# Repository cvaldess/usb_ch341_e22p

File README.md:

# usb_ch341_e22p

**USB → SPI** adapter for using an **EBYTE E22P-868M30S** LoRa module (SX1262 + PA, 30 dBm / 1 W) with **[meshtasticd](https://meshtastic.org/docs/software/linux/)** on a PC or a Raspberry Pi, with no GPIO needed.

The bridge is a **CH341F** in UIO mode, the mode supported by Meshtastic's [`libch341-spi-userspace`](https://github.com/meshtastic/libch341-spi-userspace) driver. A **TPS2115A** power multiplexer switches automatically between USB power and a DC jack, so the module can transmit at full power without overloading the computer's port.

---

## Specifications

| | |
|---|---|
| PCB | 49.22 × 63.54 mm · **2 layers** · 1.6 mm · vias 0.6/0.3 mm |
| USB bridge | CH341F (QFN-28), parallel/synchronous mode (PID `0x5512`) |
| Radio | EBYTE E22P-868M30S — SX1262 + PA, up to **30 dBm**, 868 MHz |
| Power | USB-C 5 V **or** 5 V DC jack (2.5 mm), automatic switchover |
| Current limit | 1.28 A nominal (TPS2115A with `R8` = 390 Ω) |
| Logic | 3.3 V (XC6206 LDO), the E22P's logic level |
| Antenna | Right-angle female SMA, 50 Ω |
| Configuration | 24C02 EEPROM for VID/PID/mode |

## How the power path works

This is the least obvious part of the design. The E22P draws **600–670 mA when transmitting at 30 dBm**, more than a USB port guarantees (500 mA). The board handles this with a multiplexer whose source selection is **deterministic**, not based on comparing voltages:

| USB | Jack | `D1` | `D0` | Active source | LED `D4` |
|:---:|:----:|:----:|:----:|---|:---:|
| ✅ | ❌ | 0 | 0 | **USB** — use reduced power | off |
| ✅ | ✅ | 1 | 0 | **Jack** — full power | **on** |
| ❌ | ✅ | 0 | 0 | none (Hi-Z) | — |
| ❌ | ❌ | 0 | 0 | none (Hi-Z) | — |

`D0` is tied to ground and `D1` is driven by the jack's switch contact, with `R7` (10 kΩ) pulled up to **VBUS**. So `D1` encodes *"jack present **and** USB present"*, which gives two useful properties:

- With the jack plugged in, **the jack always wins**, whichever source has the higher voltage (both useful rows use `D0`=0, where the TPS2115A truth table ignores the `IN2>IN1` comparison).
- **Without USB the module is left unpowered**, which is intended: the board is useless when disconnected from the host, and this prevents a powered E22P from back-feeding current through the pins of an unpowered CH341.

LED `D4` hangs off `STAT`, which is open-drain and pulls low when `IN1` is active: **on = running from the jack**.

## meshtasticd configuration

The CH341 pins are numbered as UIO lines `D0`–`D7`. This board's pin mapping matches the official `lora-usb-meshtoad-e22.yaml` preset:

```yaml
Lora:
  Module: sx1262
  CS: 0        # D0 · pin 15 → NSS
  RXen: 1      # D1 · pin 16 → EN   (RF front-end enable)
  Reset: 2     # D2 · pin 17 → NRST
  Busy: 4      # D4 · pin 19 → BUSY
  IRQ: 6       # D6 · pin 21 → DIO1
  spidev: ch341
  DIO2_AS_RF_SWITCH: true
  DIO3_TCXO_VOLTAGE: true
  USB_VID: 0x1A86
  USB_PID: 0x5512
  # When powered ONLY from USB, lower the power so the port is not overloaded:
  # SX126X_MAX_POWER: 10
```

`SCK` is on `D3` (pin 18) and `MOSI` on `D5` (pin 20); `MISO` is on `D7` (pin 22), which, like `D6`, is a fixed input on the CH341. `DIO2_AS_RF_SWITCH` is mandatory: on the board, the `DIO2` pin is bridged to `T/R CTRL`, as note ① of the EBYTE manual specifies.

> [!IMPORTANT]
> **EEPROM `U2` must be programmed** with `MODE = 0x12` for the CH341 to enumerate as a parallel/synchronous port. Unprogrammed, the chip reads floating `SDA`/`SCL` and boots as a **serial port**, not as SPI. It is programmed over USB with `CH341CFG` or `IMSProg`.

## Manufacturing

Everything you need is in [`fab/`](fab/):

| File | Purpose |
|---|---|
| `gerbers-pcbway.zip` | Gerbers + drill files + drill maps, ready to upload to PCBWay |
| `bom-pcbway.csv` | Bill of materials: manufacturer, part number, LCSC code and assembly notes |
| `centroid-pcbway.csv` | Placement positions for assembly (the 34 SMD parts) |
| `*-drl_map.pdf` | Drill map, for a quick visual check |
| `*.gtp` / `*.gbp` | Paste layers, in case you order a stencil |

Parameters: **2 layers, 1.6 mm, HASL or ENIG**. Nothing beyond standard capabilities. The stencil is **single-sided** (top): the bottom paste layer is empty.

### BOM notes

- **Every part has an LCSC code**, passives included. The code for `U3` (E22P-868M30S, `C51912689`) is only in the BOM, not in the schematic.
- **`SMA1` is through-hole**: it is in the BOM but not in the centroid file, and is soldered after reflow. The 4 shell legs of `USB1` are through-hole too.
- **The centroid gives the centre of each part's body.** For `U3`, `USB1` and `U6` this is not the footprint origin (it is 1.41, 1.15 and 0.65 mm away); the BOM says so in their notes.

## Main components

| Ref | Part | Function |
|---|---|---|
| `U1` | CH341F | USB ↔ SPI bridge |
| `U2` | 24C02 | Configuration EEPROM (VID/PID/mode) |
| `U3` | E22P-868M30S | SX1262 + PA LoRa module |
| `U4` | XC6206P332MR | 3.3 V LDO for the CH341 |
| `U5` | TPS2115A | Power multiplexer |
| `U6` | DC-005-2.5A | 5 V DC jack with switch contact |
| `U7` | H7VHD3UA | TVS protection on VBUS |
| `D2` | TPD4E05U06 | USB ESD protection (D+/D−/CC1/CC2) |
| `C5` | 470 µF / 16 V | Solid polymer, 28 mΩ ESR — reservoir for TX peaks |

## Datasheets

The PDFs are not included in the repository (they are copyrighted by their manufacturers). Links to the sources:

- [CH341 (WCH)](https://www.wch-ic.com/products/CH341.html) · [E22P-868M30S (EBYTE)](https://www.cdebyte.com/products/E22P-868M30S) · [TPS2115A (TI)](https://www.ti.com/product/TPS2115A) · [TPD4E05U06 (TI)](https://www.ti.com/product/TPD4E05U06) · [XC6206 (Torex)](https://www.torexsemi.com/products/voltage-regulators/xc6206/)
- LCSC references: `C412870` (CH341F) · `C2863458` (TPS2115A) · `C138714` (TPD4E05U06) · `C20615807` (H7VHD3UA) · `C709357` (USB-C) · `C2880544` (jack) · `C9002` (crystal)

## Known limitations

- **No protection on the jack input.** There is no TVS and no reverse-polarity protection on `IN1`. The E22P is damaged above 5.5 V and the TPS2115A has an absolute maximum of 6 V: a 9 V or 12 V supply, or a centre-negative one, destroys both. **Use 5 V only and check the polarity.**
- **TX power is not detected automatically.** meshtasticd does not know whether the jack is plugged in, so `SX126X_MAX_POWER` is a fixed setting. If you will only use the board on USB power, lower it.

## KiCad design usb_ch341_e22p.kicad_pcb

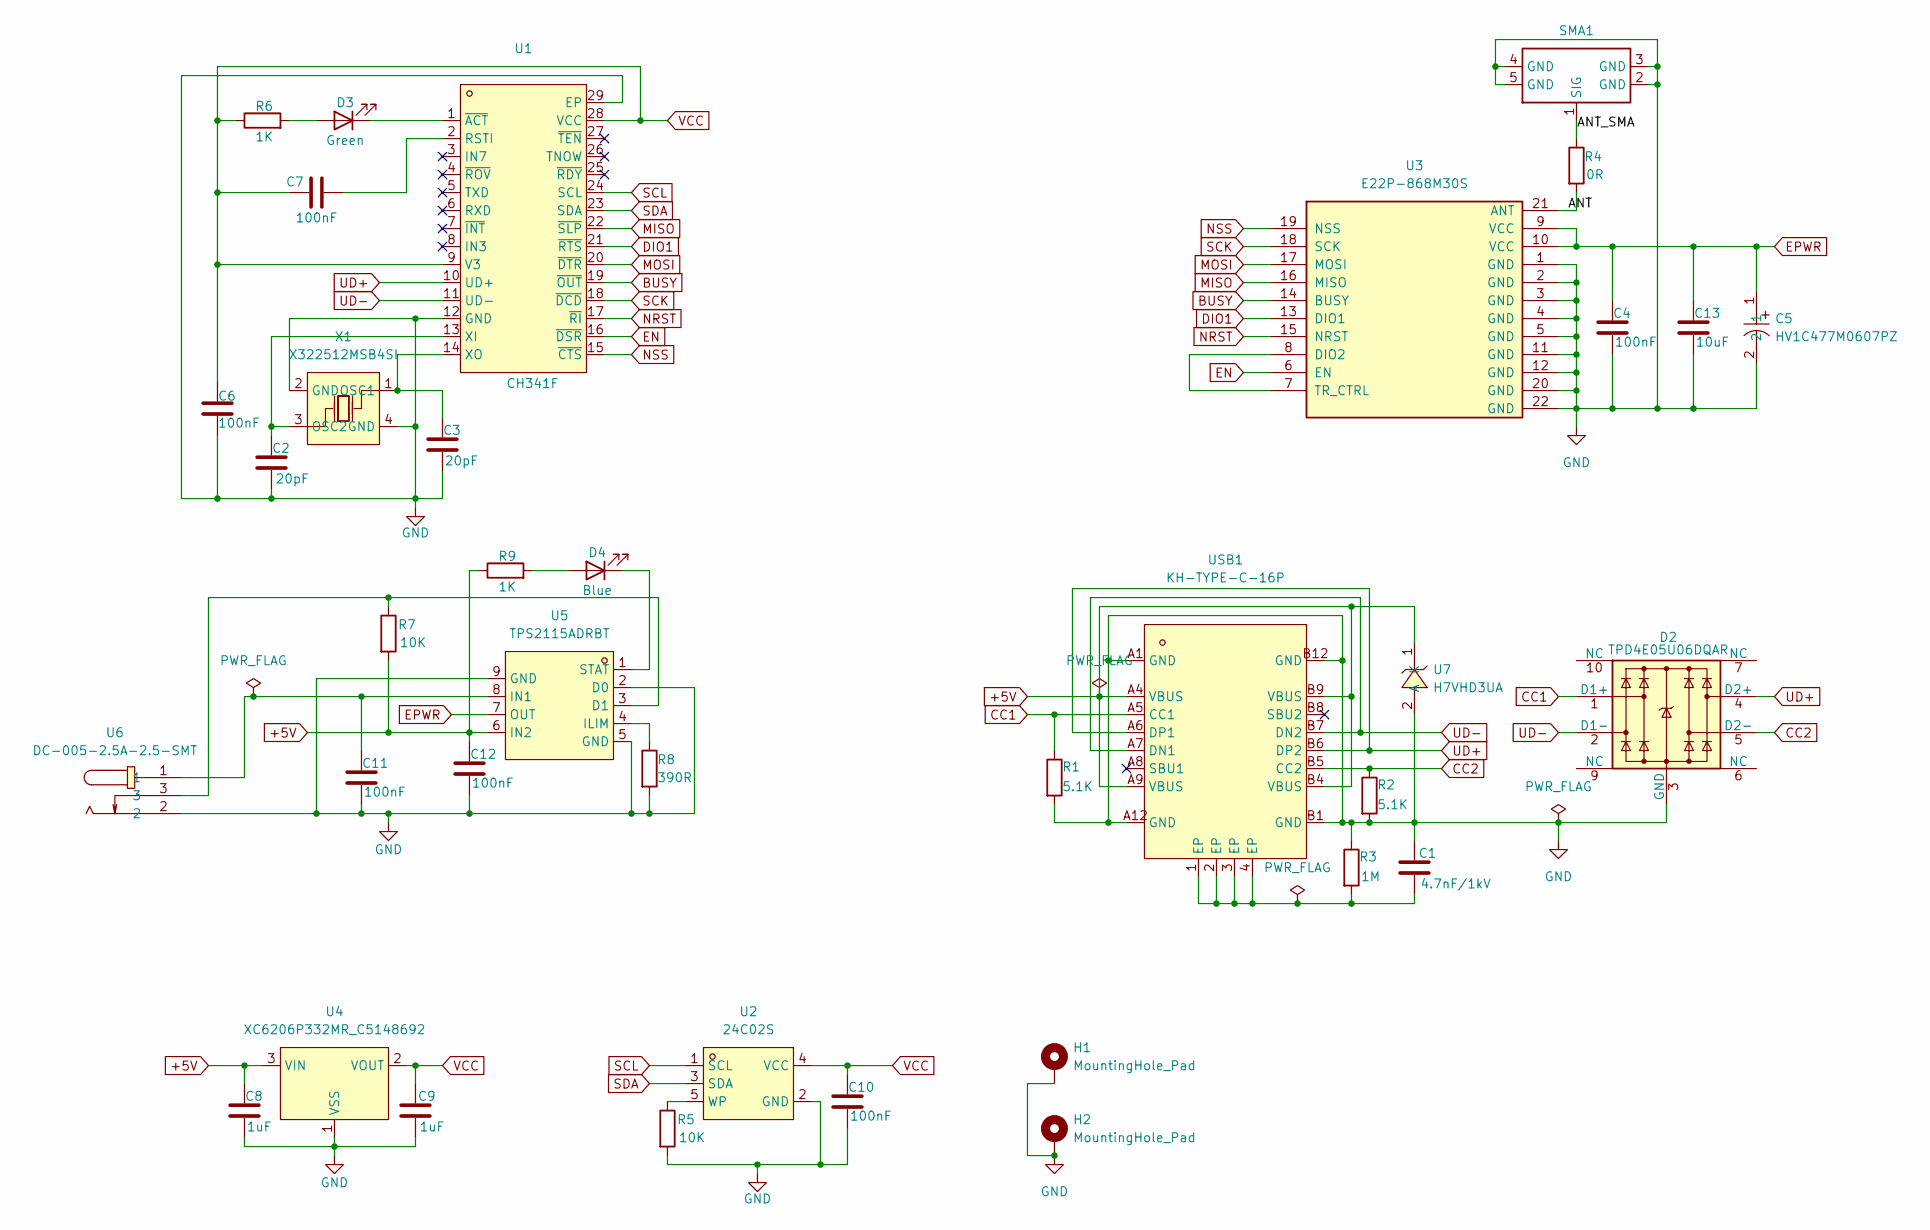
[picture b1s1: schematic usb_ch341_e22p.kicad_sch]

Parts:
C1: 4.7nF/1kV; C_1206_3216Metric; LCSC Part C9192
C2, C3: 20pF; C_0402_1005Metric; LCSC Part C5137579
C4, C6, C7, C10, C11, C12: 100nF; C_0603_1608Metric; LCSC Part C66501
C5: HV1C477M0607PZ; CAP-SMD_BD6.3-L6.6-W6.6-LS7.8-FD; MPN HV1C477M0607PZ; LCSC Part C42436549
C8, C9: 1uF; C_0603_1608Metric; LCSC Part C29936
C13: 10uF; C_0603_1608Metric; LCSC Part C3039698
D2: TPD4E05U06DQAR; USON-10_L2.5-W1.0-P0.50-BL; MPN TPD4E05U06DQAR; LCSC Part C138714
D3: Green; LED_0603_1608Metric; LCSC Part C7371903
D4: Blue; LED_0603_1608Metric; LCSC Part C7371903
H1, H2: MountingHole_Pad; MountingHole_2.5mm_Pad_Via
R1, R2: 5.1K; R_0603_1608Metric; LCSC Part C23186
R3: 1M; R_0603_1608Metric; LCSC Part C2907003
R4: 0R; R_0603_1608Metric; LCSC Part C2906974
R5, R7: 10K; R_0603_1608Metric; LCSC Part C2906982
R6, R9: 1K; R_0603_1608Metric; LCSC Part C2907002
R8: 390R; R_0603_1608Metric; LCSC Part C2907159
SMA1: -; SMA-TH_HJ-SMA175; Manufacturer Part HJ-SMA175; LCSC Part Name 两件套 内孔 SMA 弯头
U1: CH341F; QFN-28_L4.0-W4.0-P0.40-BL-EP; MPN CH341F; LCSC Part C412870
U2: 24C02S; SOT-23-5_L3.0-W1.6-P0.95-LS2.8-BR; MPN 24C02S(XBLW); LCSC Part C18723540
U3: E22P-868M30S; PE22(900M30S); MPN E22P-868M30S
U4: XC6206P332MR_C5148692; SOT-23-3_L2.9-W1.3-P1.90-LS2.4-BR; MPN XC6206P332MR; LCSC Part C5148692
U5: TPS2115ADRBT; SON-8_L3.0-W3.0-P0.65-TL-EP; MPN TPS2115ADRBT; LCSC Part C2863458
U6: DC-005-2.5A-2.5-SMT; DC-IN-TH_XKB_DC-005-2.5A-2.5-SMT; MPN DC-005-2.5A-2.5-SMT; LCSC Part C2880544
U7: H7VHD3UA; SOD-323_L1.7-W1.3-LS2.7-RD; MPN H7VHD3UA; LCSC Part C20615807
USB1: KH-TYPE-C-16P; USB-C-SMD_KH-TYPE-C-16P; MPN KH-TYPE-C-16P; LCSC Part C709357
X1: X322512MSB4SI; CRYSTAL-SMD_4P-L3.2-W2.5-BL; MPN X322512MSB4SI; LCSC Part C9002

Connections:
+5V: C8.1, C12.1, R7.2, R9.1, U4.3 (VIN), U5.6 (IN2), U7.1 (K), USB1.A4 (VBUS), USB1.A9 (VBUS), USB1.B4 (VBUS), USB1.B9 (VBUS)
/ANT: R4.2, U3.21 (ANT)
/ANT_SMA: R4.1, SMA1.1 (SIG)
BUSY: U1.19 (~OUT), U3.14 (BUSY)
CC1: D2.1 (D1+), R1.1, USB1.A5 (CC1)
CC2: D2.5 (D2-), R2.1, USB1.B5 (CC2)
DIO1: U1.21 (~RTS), U3.13 (DIO1)
EN: U1.16 (~DSR), U3.6 (EN)
EPWR: C4.1, C5.1, C13.1, U3.9 (VCC), U3.10 (VCC), U5.7 (OUT)
GND: C1.1, C2.2, C3.2, C4.2, C5.2, C6.2, C8.2, C9.2, C10.2, C11.2, C12.2, C13.2, D2.3 (GND), D2.8 (GND), H1.1 (1_1), H2.1 (1_1), R1.2, R2.2, R3.1, R5.2, R8.2, SMA1.2 (GND), SMA1.3 (GND), SMA1.4 (GND), SMA1.5 (GND), U1.12 (GND), U1.29 (EP), U2.2 (GND), U3.1 (GND), U3.2 (GND), U3.3 (GND), U3.4 (GND), U3.5 (GND), U3.11 (GND), U3.12 (GND), U3.20 (GND), U3.22 (GND), U4.1 (VSS), U5.2 (D0), U5.5 (GND), U5.9 (GND), U6.2, U7.2 (A), USB1.A1 (GND), USB1.A12 (GND), USB1.B1 (GND), USB1.B12 (GND), X1.2 (GND), X1.4 (GND)
MISO: U1.22 (~SLP), U3.16 (MISO)
MOSI: U1.20 (~DTR), U3.17 (MOSI)
NRST: U1.17 (~RI), U3.15 (NRST)
NSS: U1.15 (~CTS), U3.19 (NSS)
unnamed: C1.2, R3.2, USB1.1 (EP), USB1.2 (EP), USB1.3 (EP), USB1.4 (EP)
unnamed: D3.2 (A), R6.2
unnamed: D3.1 (K), U1.1 (~ACT)
unnamed: D4.2 (A), R9.2
unnamed: D4.1 (K), U5.1 (STAT)
unnamed: C7.1, U1.2 (RSTI)
unnamed: C2.1, U1.13 (XI), X1.3 (OSC2)
unnamed: C3.1, U1.14 (XO), X1.1 (OSC1)
unnamed: R5.1, U2.5 (WP)
unnamed: U3.7 (TR_CTRL), U3.8 (DIO2)
unnamed: R7.1, U5.3 (D1), U6.3
unnamed: R8.1, U5.4 (ILIM)
unnamed: C11.1, U5.8 (IN1), U6.1
SCK: U1.18 (~DCD), U3.18 (SCK)
SCL: U1.24 (SCL), U2.1 (SCL)
SDA: U1.23 (SDA), U2.3 (SDA)
UD+: D2.4 (D2+), U1.10 (UD+), USB1.A6 (DP1), USB1.B6 (DP2)
UD-: D2.2 (D1-), U1.11 (UD-), USB1.A7 (DN1), USB1.B7 (DN2)
VCC: C6.1, C7.2, C9.1, C10.1, R6.1, U1.9 (V3), U1.28 (VCC), U2.4 (VCC), U4.2 (VOUT)

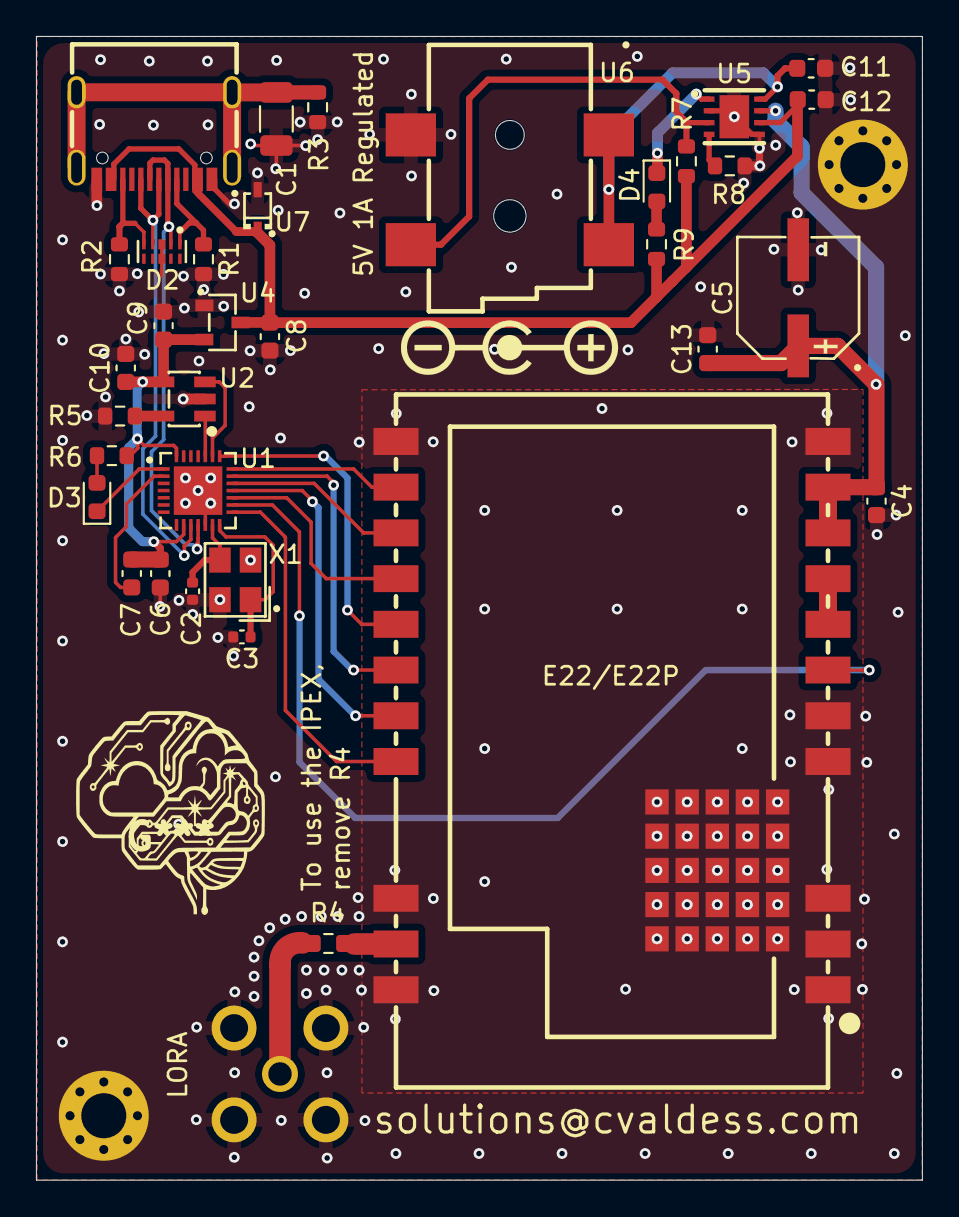
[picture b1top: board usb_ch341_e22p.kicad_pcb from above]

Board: 2 copper layers, 49.2 x 63.5 mm, 37 parts (0 on the bottom side), 33 nets.
